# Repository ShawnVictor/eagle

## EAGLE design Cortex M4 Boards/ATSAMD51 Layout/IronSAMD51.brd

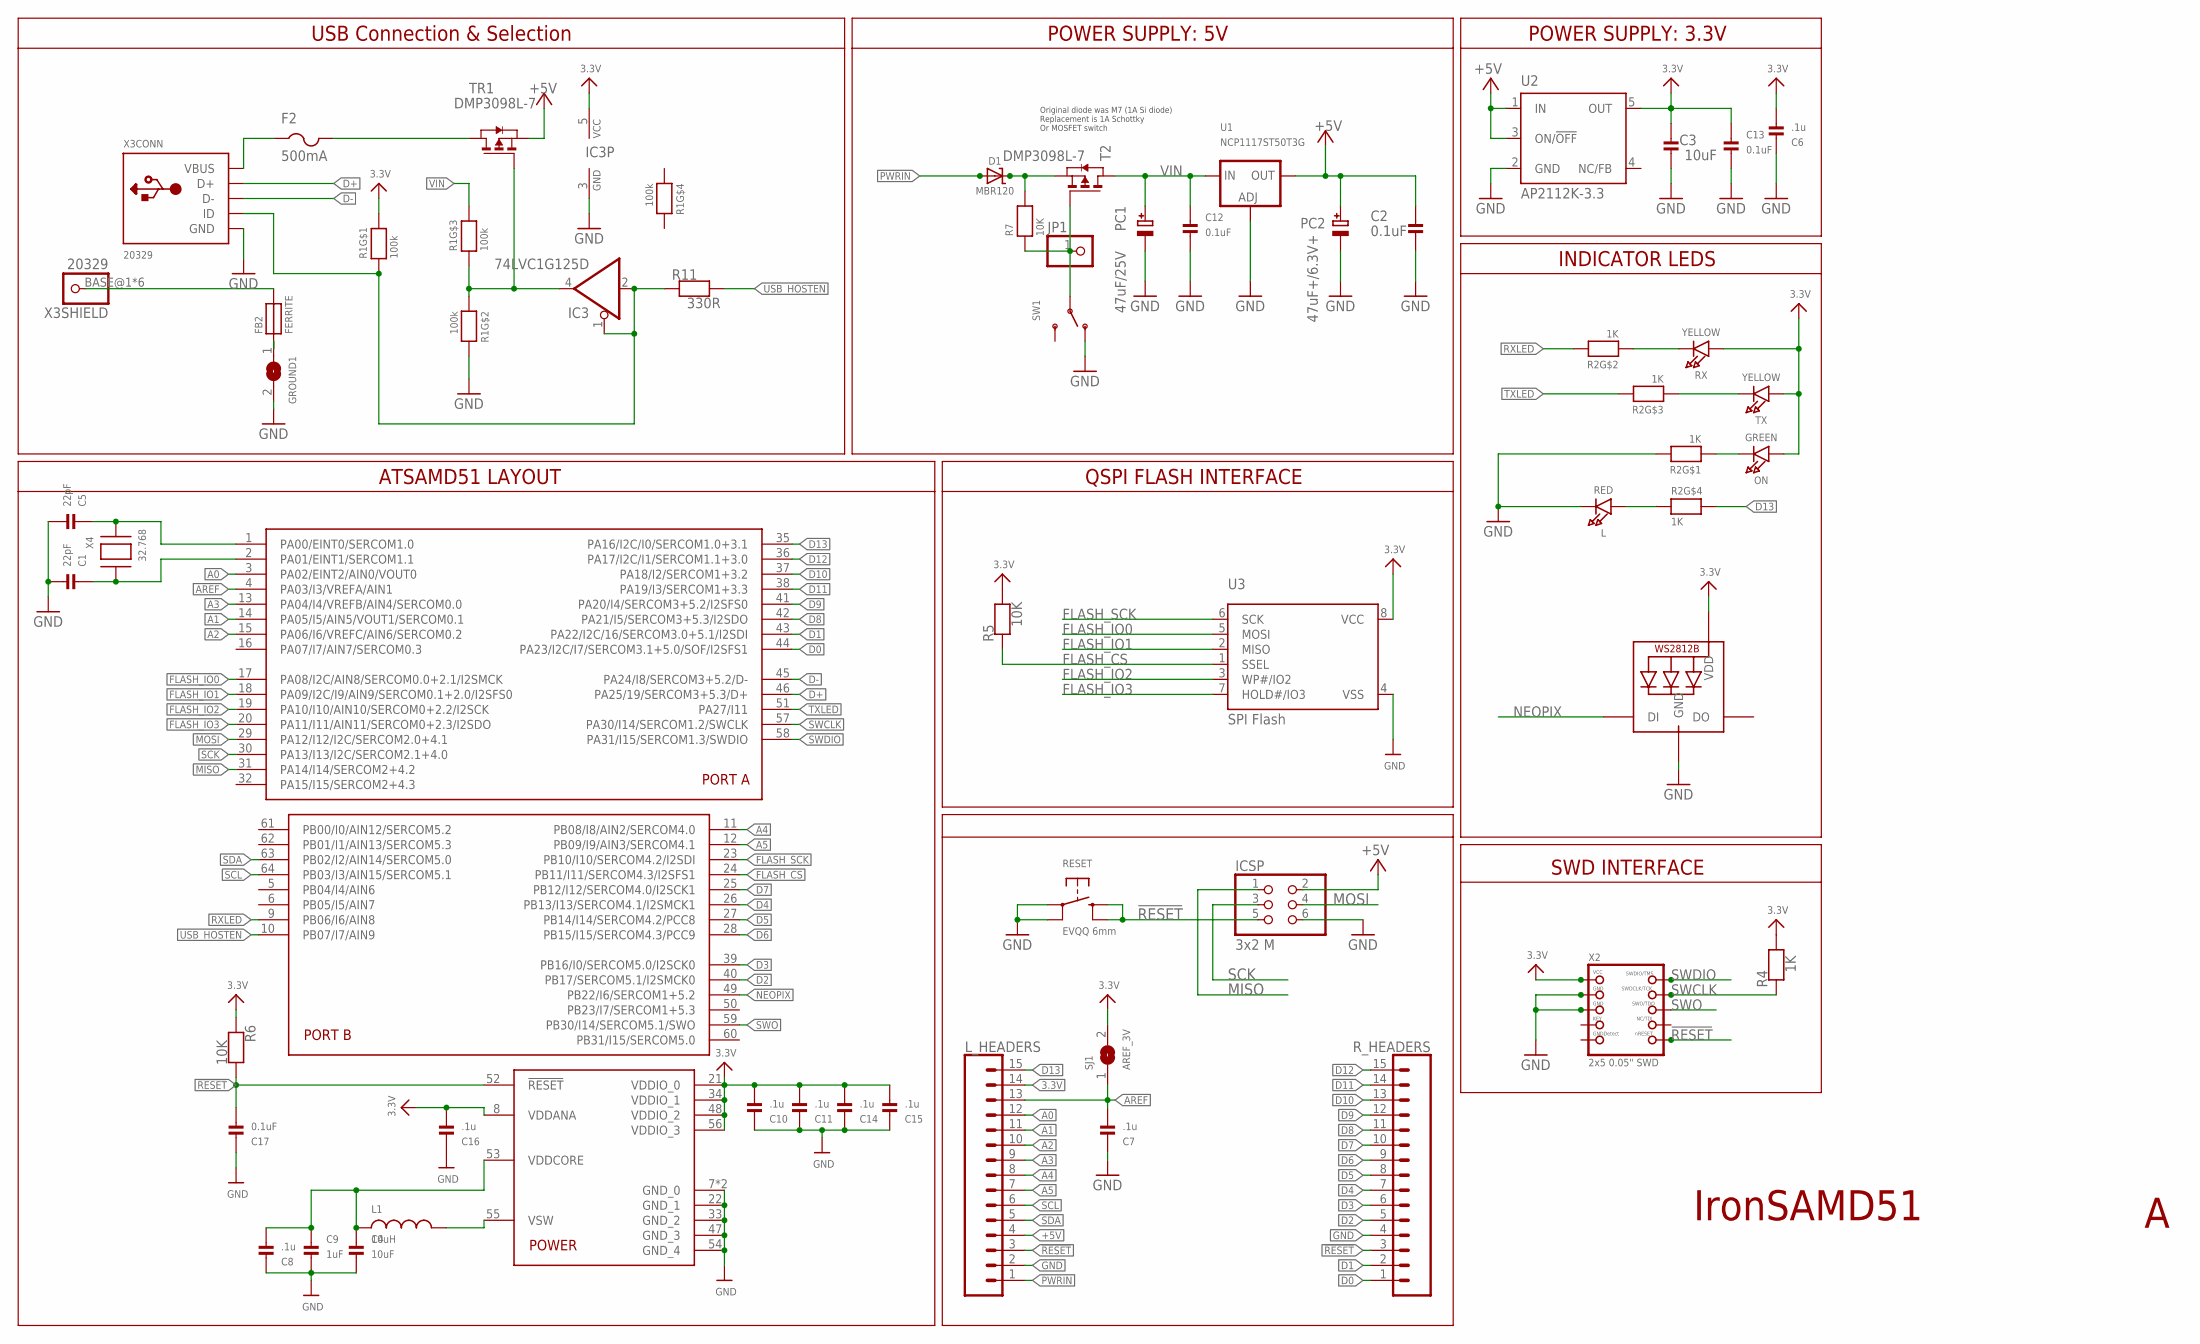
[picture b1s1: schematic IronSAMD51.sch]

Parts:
C1, C5: 22pF; 0603
C2: 0.1uF; 0805
C3, C4: 10uF; 0805
C6, C7, C8, C10, C11, C14, C15, C16: .1u; 0603
C9: 1uF; 0603
C12, C13, C17: 0.1uF; 0603
D1: MBR120; SOD-123
F2: 500mA; R1206
FB2: FERRITE; 0603
GROUND1: SOLDERJUMPERCLOSED; SOLDERJUMPER_CLOSEDWIRE
IC3: 74LVC1G125D; SOT23-5
ICSP: 3x2 M; 2X03_ROUND_70MIL
JP1: HEADER-1X1ROUND; 1X01_ROUND
L: RED; CHIPLED_0805_NOOUTLINE
L1: 10uH; INDUCTOR_1007
LED1: WS2812B3535; LED3535
L_HEADERS: CONN_15; 1X15
ON: GREEN; CHIPLED_0805_NOOUTLINE
PC1: 47uF/25V; PANASONIC_D
PC2: 47uF+/6.3V+; PANASONIC_D
R1: 100k; RESPACK_4X0603
R2: 1K; RESPACK_4X0603
R4: 1K; 0603
R5, R6, R7: 10K; 0603
R11: 330R; 0603
RESET: EVQQ 6mm; EVQ-Q2
RX: YELLOW; CHIPLED_0805_NOOUTLINE
R_HEADERS: CONN_15; 1X15
SJ1: AREF_3V; SOLDERJUMPER_CLOSEDWIRE
SW1: SWITCH_SPDT; SPDT_SMT_SSSS811101
T2: DMP3098L-7; SOT-23
TR1: DMP3098L-7; SOT-23
TX: YELLOW; CHIPLED_0805_NOOUTLINE
U1: NCP1117ST50T3G; SOT223-R
U2: AP2112K-3.3; SOT23-DBV
U3: SPI Flash; SOIC8_208MIL
U$3: ATSAMD51J; PQFN64-1
X2: 2x5 0.05" SWD; 2X05_1.27MM_BOX_POSTS
X3: 20329; 4UCONN_20329_V2
X4: 32.768; XTAL3215

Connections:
3.3V: C3.2, C6.2, C10.2, C11.2, C13.1, C14.2, C15.2, C16.2, IC3.5 (VCC), LED1.2 (VDD), L_HEADERS.14, ON.A, R1.8 (2), R4.2, R5.2, R6.1, RX.A, SJ1.2, TX.A, U2.5 (OUT), U3.8 (VCC), U$3.8 (VDDANA), U$3.21 (VDDIO_0), U$3.34 (VDDIO_1), U$3.48 (VDDIO_2), U$3.56 (VDDIO_3), X2.1 (VCC)
!RESET: C17.2, ICSP.5, L_HEADERS.3, R6.2, RESET.B (S), RESET.B' (S1), R_HEADERS.3, U$3.52 (!RESET), X2.10 (NRESET)
+5V: C2.2, ICSP.2, L_HEADERS.4, PC2.+, TR1.2 (S), U1.2 (OUT), U1.4 (OUT), U2.1 (IN), U2.3 (ON/!OFF)
A0: L_HEADERS.12, U$3.3 (PA02/EINT2/AIN0/VOUT0)
A1: L_HEADERS.11, U$3.14 (PA05/I5/AIN5/VOUT1/SERCOM0.1)
A2: L_HEADERS.10, U$3.15 (PA06/I6/VREFC/AIN6/SERCOM0.2)
A3: L_HEADERS.9, U$3.13 (PA04/I4/VREFB/AIN4/SERCOM0.0)
A4: L_HEADERS.8, U$3.11 (PB08/I8/AIN2/SERCOM4.0)
A5: L_HEADERS.7, U$3.12 (PB09/I9/AIN3/SERCOM4.1)
AREF: C7.2, L_HEADERS.13, SJ1.1, U$3.4 (PA03/I3/VREFA/AIN1)
D0: R_HEADERS.1, U$3.44 (PA23/I2C/I7/SERCOM3.1+5.0/SOF/I2SFS1)
D1: R_HEADERS.2, U$3.43 (PA22/I2C/16/SERCOM3.0+5.1/I2SDI)
D2: R_HEADERS.5, U$3.40 (PB17/SERCOM5.1/I2SMCK0)
D3: R_HEADERS.6, U$3.39 (PB16/I0/SERCOM5.0/I2SCK0)
D4: R_HEADERS.7, U$3.26 (PB13/I13/SERCOM4.1/I2SMCK1)
D5: R_HEADERS.8, U$3.27 (PB14/I14/SERCOM4.2/PCC8)
D6: R_HEADERS.9, U$3.28 (PB15/I15/SERCOM4.3/PCC9)
D7: R_HEADERS.10, U$3.25 (PB12/I12/SERCOM4.0/I2SCK1)
D8: R_HEADERS.11, U$3.42 (PA21/I5/SERCOM3+5.3/I2SDO)
D9: R_HEADERS.12, U$3.41 (PA20/I4/SERCOM3+5.2/I2SFS0)
D10: R_HEADERS.13, U$3.37 (PA18/I2/SERCOM1+3.2)
D11: R_HEADERS.14, U$3.38 (PA19/I3/SERCOM1+3.3)
D12: R_HEADERS.15, U$3.36 (PA17/I2C/I1/SERCOM1.1+3.0)
D13: L_HEADERS.15, R2.5 (2), U$3.35 (PA16/I2C/I0/SERCOM1.0+3.1)
D+: U$3.46 (PA25/19/SERCOM3+5.3/D+), X3.D+
D-: U$3.45 (PA24/I8/SERCOM3+5.2/D-), X3.D-
FLASH_CS: R5.1, U3.1 (SSEL), U$3.24 (PB11/I11/SERCOM4.3/I2SFS1)
FLASH_IO0: U3.5 (MOSI), U$3.17 (PA08/I2C/AIN8/SERCOM0.0+2.1/I2SMCK)
FLASH_IO1: U3.2 (MISO), U$3.18 (PA09/I2C/I9/AIN9/SERCOM0.1+2.0/I2SFS0)
FLASH_IO2: U3.3 (WP#/IO2), U$3.19 (PA10/I10/AIN10/SERCOM0+2.2/I2SCK)
FLASH_IO3: U3.7 (HOLD#/IO3), U$3.20 (PA11/I11/AIN11/SERCOM0+2.3/I2SDO)
FLASH_SCK: U3.6 (SCK), U$3.23 (PB10/I10/SERCOM4.2/I2SDI)
GND: C1.2, C2.1, C3.1, C4.2, C5.2, C6.1, C7.1, C8.1, C9.2, C10.1, C11.1, C12.2, C13.2, C14.1, C15.1, C16.1, C17.1, GROUND1.2, IC3.3 (GND), ICSP.6, L.C, LED1.4 (GND), L_HEADERS.2, PC1.-, PC2.-, R1.7 (2), R2.8 (2), RESET.A, RESET.A' (P1), R_HEADERS.4, SW1.A (O), U1.1 (ADJ), U2.2 (GND), U3.4 (VSS), U$3.7 (GND_0), U$3.22 (GND_1), U$3.33 (GND_2), U$3.47 (GND_3), U$3.54 (GND_4), U$3.EXP (GND_0), X2.3 (GND), X2.5 (GND), X3.GND
MISO: ICSP.1, U$3.31 (PA14/I14/SERCOM2+4.2)
MOSI: ICSP.4, U$3.29 (PA12/I12/I2C/SERCOM2.0+4.1)
unnamed: F2.1, X3.VBUS
unnamed: F2.2, TR1.1 (D)
unnamed: IC3.4 (O), R1.2 (1), R1.3 (1), TR1.3 (G)
unnamed: ON.C, R2.1
unnamed: FB2.1, GROUND1.1
unnamed: R2.2 (1), RX.C
unnamed: R2.3 (1), TX.C
unnamed: L.A, R2.4 (1)
unnamed: IC3.1 (OE), IC3.2 (I), R1.1, R11.1, X3.ID
unnamed: C5.1, U$3.1 (PA00/EINT0/SERCOM1.0), X4.P$1
unnamed: C1.1, U$3.2 (PA01/EINT1/SERCOM1.1), X4.P$2
unnamed: L1.P$2 (2), U$3.55 (VSW)
unnamed: C4.1, C8.2, C9.1, L1.P$1 (1), U$3.53 (VDDCORE)
unnamed: D1.C, R7.2, T2.2 (S)
NEOPIX: LED1.1 (DI), U$3.49 (PB22/I6/SERCOM1+5.2)
PWRIN: D1.A, L_HEADERS.1
PWR_SWITCH: JP1.1, R7.1, SW1.B, T2.3 (G)
RXLED: R2.7 (2), U$3.9 (PB06/I6/AIN8)
SCK: ICSP.3, U$3.30 (PA13/I13/I2C/SERCOM2.1+4.0)
SCL: L_HEADERS.6, U$3.64 (PB03/I3/AIN15/SERCOM5.1)
SDA: L_HEADERS.5, U$3.63 (PB02/I2/AIN14/SERCOM5.0)
SWCLK: R4.1, U$3.57 (PA30/I14/SERCOM1.2/SWCLK), X2.4 (SWDCLK)
SWDIO: U$3.58 (PA31/I15/SERCOM1.3/SWDIO), X2.2 (SWDIO)
SWO: U$3.59 (PB30/I14/SERCOM5.1/SWO), X2.6 (SWO)
TXLED: R2.6 (2), U$3.51 (PA27/I11)
USB_HOSTEN: R11.2, U$3.10 (PB07/I7/AIN9)
USHIELD: FB2.2, X3.BASE@1 (1), X3.BASE@2 (1), X3.SPRT@1 (1), X3.SPRT@2 (1), X3.SPRT@3 (1), X3.SPRT@4 (1)
VIN: C12.1, PC1.+, R1.6 (2), T2.1 (D), U1.3 (IN)

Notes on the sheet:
USB Connection & Selection
Original diode was M7 (1A Si diode) Replacement is 1A Schottky Or MOSFET switch
POWER SUPPLY: 5V
INDICATOR LEDS
POWER SUPPLY: 3.3V
SWD INTERFACE
QSPI FLASH INTERFACE
ATSAMD51 LAYOUT
IronSAMD51

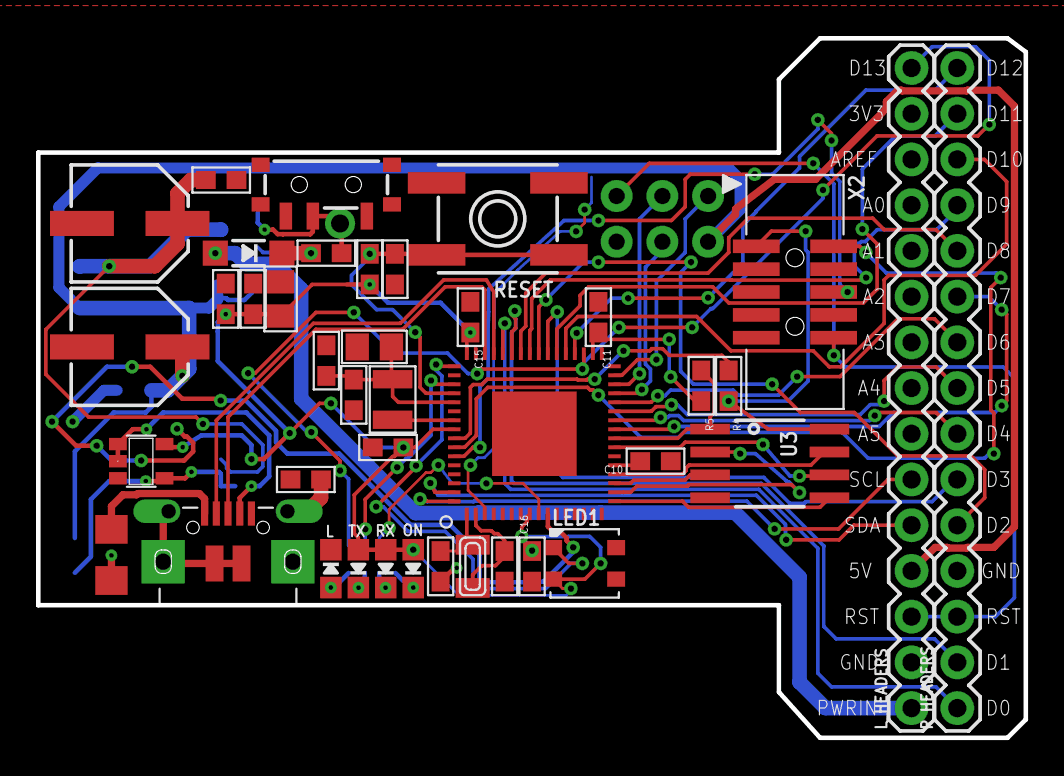
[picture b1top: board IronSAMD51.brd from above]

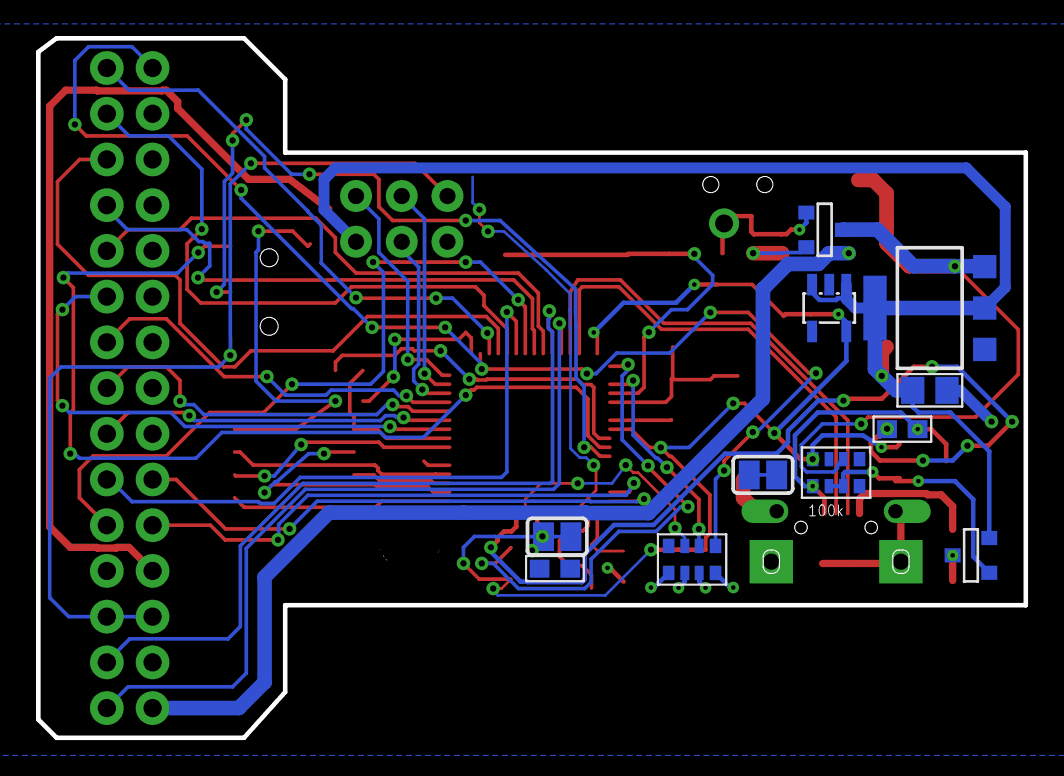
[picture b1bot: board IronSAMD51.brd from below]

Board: 2 copper layers, 54.9 x 38.9 mm, 53 parts (11 on the bottom side), 63 nets.

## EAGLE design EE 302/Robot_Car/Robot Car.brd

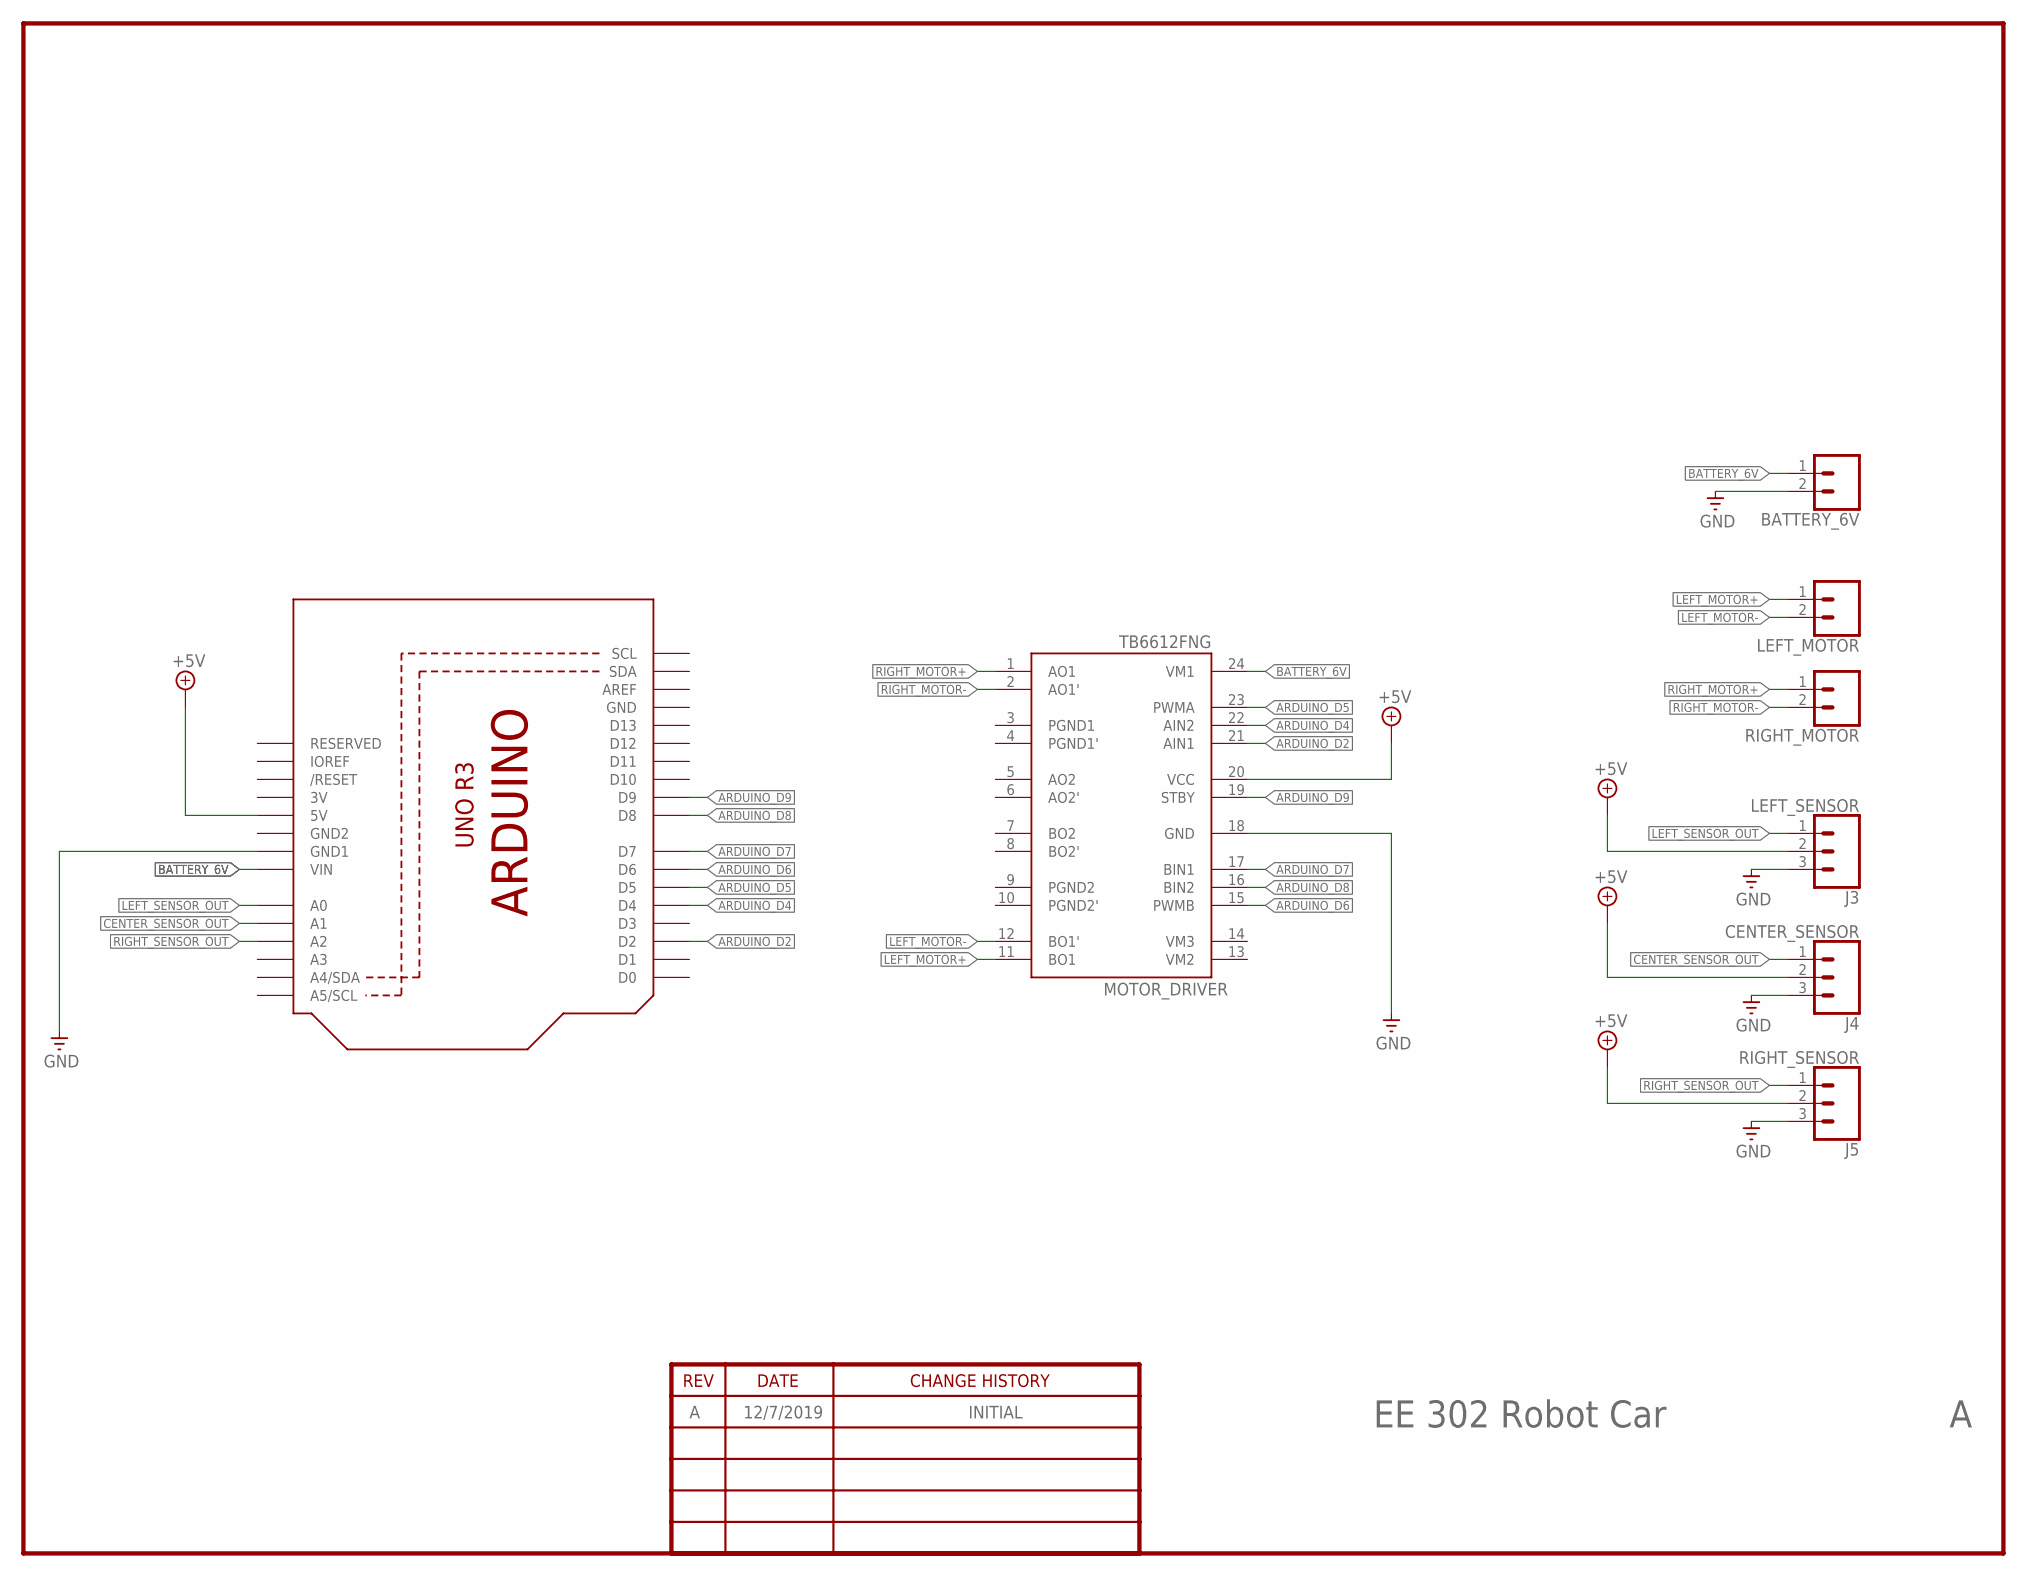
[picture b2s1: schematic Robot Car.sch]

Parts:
BATTERY_6V: CONN_02; 1X02
J3: LEFT_SENSOR; 1X03
J4: CENTER_SENSOR; 1X03
J5: RIGHT_SENSOR; 1X03
LEFT_MOTOR: CONN_02; 1X02
MOTOR_DRIVER: TB6612FNG; SSOP24
RIGHT_MOTOR: CONN_02; 1X02
U1: ARDUINOR3-DIMENSION; ARDUINOR3

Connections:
3V: U1.3V
+5V: J3.2, J4.2, J5.2, MOTOR_DRIVER.20 (VCC), U1.5V
ARDUINO_D2: MOTOR_DRIVER.21 (AIN1), U1.D2
ARDUINO_D4: MOTOR_DRIVER.22 (AIN2), U1.D4
ARDUINO_D5: MOTOR_DRIVER.23 (PWMA), U1.D5
ARDUINO_D6: MOTOR_DRIVER.15 (PWMB), U1.D6
ARDUINO_D7: MOTOR_DRIVER.17 (BIN1), U1.D7
ARDUINO_D8: MOTOR_DRIVER.16 (BIN2), U1.D8
ARDUINO_D9: MOTOR_DRIVER.19 (STBY), U1.D9
BATTERY_6V: BATTERY_6V.1, MOTOR_DRIVER.24 (VM1), U1.VIN
CENTER_SENSOR_OUT: J4.1, U1.A1
GND: BATTERY_6V.2, J3.3, J4.3, J5.3, MOTOR_DRIVER.18 (GND), U1.GND, U1.GND1
GND2: U1.GND2
LEFT_MOTOR+: LEFT_MOTOR.1, MOTOR_DRIVER.11 (BO1)
LEFT_MOTOR-: LEFT_MOTOR.2, MOTOR_DRIVER.12 (BO1')
LEFT_SENSOR_OUT: J3.1, U1.A0
PGND1: MOTOR_DRIVER.3 (PGND1)
PGND1': MOTOR_DRIVER.4 (PGND1')
PGND2: MOTOR_DRIVER.9 (PGND2)
PGND2': MOTOR_DRIVER.10 (PGND2')
RIGHT_MOTOR+: MOTOR_DRIVER.1 (AO1), RIGHT_MOTOR.1
RIGHT_MOTOR-: MOTOR_DRIVER.2 (AO1'), RIGHT_MOTOR.2
RIGHT_SENSOR_OUT: J5.1, U1.A2
VM2: MOTOR_DRIVER.13 (VM2)
VM3: MOTOR_DRIVER.14 (VM3)

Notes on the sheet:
EE 302 Robot Car
12/7/2019
INITIAL

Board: 2 copper layers, 8 parts (0 on the bottom side), 17 nets, no tracks yet.

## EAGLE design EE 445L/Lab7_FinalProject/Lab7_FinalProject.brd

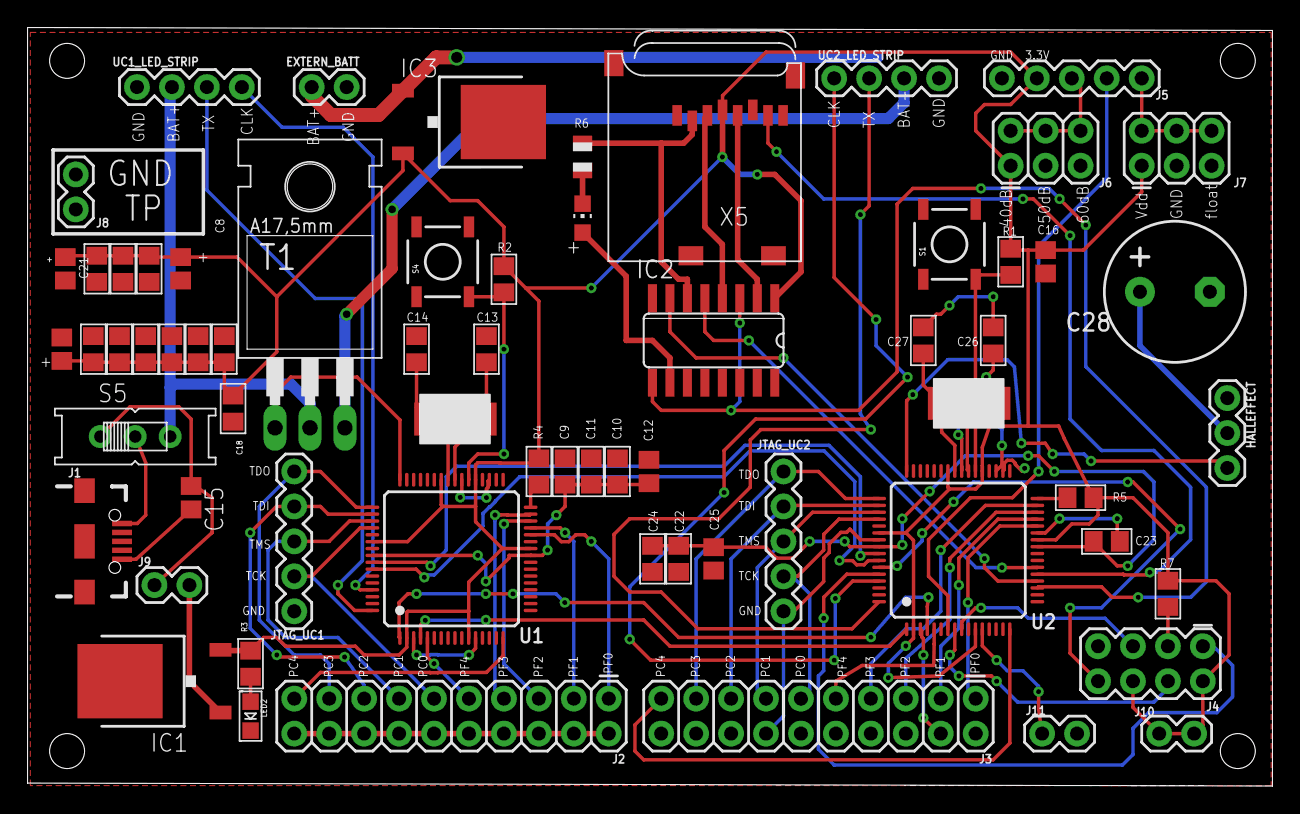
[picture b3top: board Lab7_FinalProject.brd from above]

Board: 2 copper layers, 90.5 x 55.1 mm, 66 parts (0 on the bottom side), 65 nets.

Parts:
ACT: RED; CHIP-LED0805
C1, C3, C5, C18: 0.01uF; 0805
C2: 10uF/10V; C0805
C4, C6, C9, C10, C17, C19, C22, C23: 0.1uF; 0805
C7, C11, C20, C24: 1uF; 0805
C8, C21: 0.01uF; C0805
C12, C25: 2.2uF; C0805
C13, C14, C26, C27: 10pF; 0805
C15: 4.7uF; C0805
C16: 4,7uF; C0805
C28: 1000uF; E-050X100
EXTERN_BATT: 1X02
HALLEFFECT: 1X03
IC1: 7812DT; TO252
IC2: 4050D; SO16
IC3: 3.3VReg1; TO252
J1: USB-B-MICRO-SMD
J2: LA1; 2X10
J3: LA2; 2X10
J4: ESP8266; 2X4
J5: MICROPHONE; 1X05
J6: GAIN SELECT; 2X3
J7: A/R SELECT; 2X3
J8, J9: 1X02
J10: 3.3V TESTPOINT; 1X02
J11: GND TESTPOINT; 1X02
JTAG_UC1, JTAG_UC2: 1X05
LED2: CHIPLED_0805
R1, R2, R7: 10k; 0805
R3: 1k; 0805
R4, R5: 1M; 0805
R6: 1K; R0805
S1, S4: MOMENTARY_SW; TACTILE_SWITCH_SMD
S5: EG1218
T1: TIP31; TO220
U1, U2: TM4C123GH6PM; LQFP64
U$45, U$48: NX5032GA-16MHZCRYSTAL
UC1_LED_STRIP, UC2_LED_STRIP: 1X04
X5: MICROSD

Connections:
3.3V: C1.1, C2.1, C3.1, C4.1, C5.1, C6.1, C7.1, C8.1, C16.1, C17.1, C18.1, C19.1, C20.1, C21.1, IC1.2, IC2.1, IC3.2, J4.2, J4.6, J5.4, J6.1, J7.1, J10.1, J10.2, R1.2, R2.2, R3.2, R4.2, R5.2, R7.2, U1.2, U1.11, U1.26, U1.37, U1.42, U1.54, U2.2, U2.11, U2.26, U2.37, U2.42, U2.54, X5.4
BATT_IN: C28.+, EXTERN_BATT.2, HALLEFFECT.2, IC3.1, S5.S, T1.2, UC1_LED_STRIP.3
ESP_GPIO0: J4.3, R7.1
GND: C1.2, C2.2, C3.2, C4.2, C5.2, C6.2, C7.2, C8.2, C9.2, C10.2, C11.2, C12.2, C13.1, C14.1, C15.2, C16.2, C17.2, C18.2, C19.2, C20.2, C21.2, C22.2, C23.2, C24.2, C25.2, C26.1, C27.1, C28.-, EXTERN_BATT.1, HALLEFFECT.1, IC1.3, IC2.8, IC2.11, IC2.14, IC3.3, J1.GND, J2.2, J2.4, J2.6, J2.8, J2.10, J2.12, J2.14, J2.16, J2.18, J2.20, J3.2, J3.4, J3.6, J3.8, J3.10, J3.12, J3.14, J3.16, J3.18, J3.20, J4.7, J5.5, J6.3, J7.3, J8.1, J8.2, J11.1, J11.2, JTAG_UC1.1, JTAG_UC2.1, LED2.C, S1.1, S4.1, U1.3, U1.12, U1.27, U1.34, U1.35, U1.39, U1.55, U2.3, U2.12, U2.27, U2.34, U2.35, U2.39, U2.55, UC1_LED_STRIP.4, UC2_LED_STRIP.4, X5.6, X5.MT1, X5.MT2
LED_PW_IN: T1.3, UC2_LED_STRIP.3
MIC_AR: J5.1, J7.2, J7.4, J7.6
MIC_GAIN: J5.3, J6.2, J6.4, J6.6
unnamed: C13.2, U1.40, U$45.P$1
unnamed: C9.1, C10.1, C11.1, C12.1, U1.25, U1.56
unnamed: C26.2, U2.40, U$48.P$1
unnamed: ACT.A, IC2.10
unnamed: IC2.2, X5.5
unnamed: C22.1, C23.1, C24.1, C25.1, U2.25, U2.56
unnamed: C27.2, U2.41, U$48.P$2
unnamed: R1.1, S1.3, U2.38
unnamed: R5.1, U2.32
unnamed: IC2.6, R6.1, X5.2
unnamed: ACT.C, R6.2
unnamed: IC2.4, X5.3
unnamed: IC1.1, J9.2
OSC1: C14.2, U1.41, U$45.P$2
POWER_IN: C15.1, J9.1, S5.O
POWER_LED: LED2.A, R3.1
RESET: R2.1, S4.3, U1.38
UC1_PB3/LED_SW: T1.1, U1.48
UC1_PC0/TCK: J2.11, JTAG_UC1.2, U1.52
UC1_PC1/TMS: J2.13, JTAG_UC1.3, U1.51
UC1_PC2/TDI: J2.15, JTAG_UC1.4, U1.50
UC1_PC3/TDO: J2.17, JTAG_UC1.5, U1.49
UC1_PC4: J2.19, U1.16
UC1_PD0/SSI3_CLK: U1.61, UC1_LED_STRIP.1
UC1_PD3/SSI3_TX: U1.64, UC1_LED_STRIP.2
UC1_PF0: J2.1, U1.28
UC1_PF1: J2.3, U1.29
UC1_PF2: J2.5, U1.30
UC1_PF3: J2.7, U1.31
UC1_PF4: J2.9, U1.5
UC2_PA2/SDCARD_CLK: IC2.3, IC2.9, U2.19
UC2_PA3/SDCARD_CS: IC2.7, U2.20
UC2_PA4/SDCARD_DO: U2.21, X5.7
UC2_PA5/SDCARD_DI: IC2.5, U2.22
UC2_PB3/HALLEFFECT: HALLEFFECT.3, U2.48
UC2_PC0/TCK: J3.11, JTAG_UC2.2, U2.52
UC2_PC1/TMS: J3.13, JTAG_UC2.3, U2.51
UC2_PC2/TDI: J3.15, JTAG_UC2.4, U2.50
UC2_PC3/TDO: J3.17, JTAG_UC2.5, U2.49
UC2_PC4: J3.19, U2.16
UC2_PD0/SSI3_CLK: U2.61, UC2_LED_STRIP.1
UC2_PD3/SSI3_TX: U2.64, UC2_LED_STRIP.2
UC2_PE0/ESP_GPIO2: J4.5, U2.9
UC2_PE1/ESP_RESET: J4.4, U2.8
UC2_PE2/MIC_OUT: J5.2, U2.7
UC2_PE4/ESP_TX: J4.8, U2.59
UC2_PE5/ESP_RX: J4.1, U2.60
UC2_PF0: J3.1, U2.28
UC2_PF1: J3.3, U2.29
UC2_PF2: J3.5, U2.30
UC2_PF3: J3.7, U2.31
UC2_PF4: J3.9, U2.5
UC12_PB4/CLK: U1.58, U2.58
UC12_PB5/FSS: U1.57, U2.57
UC12_PB6/7/RX2TX: U1.1, U2.4
UC12_PB6/7/TX2RX: U1.4, U2.1
VBUS: J1.VBUS, S5.P
WAKE: R4.1, U1.32

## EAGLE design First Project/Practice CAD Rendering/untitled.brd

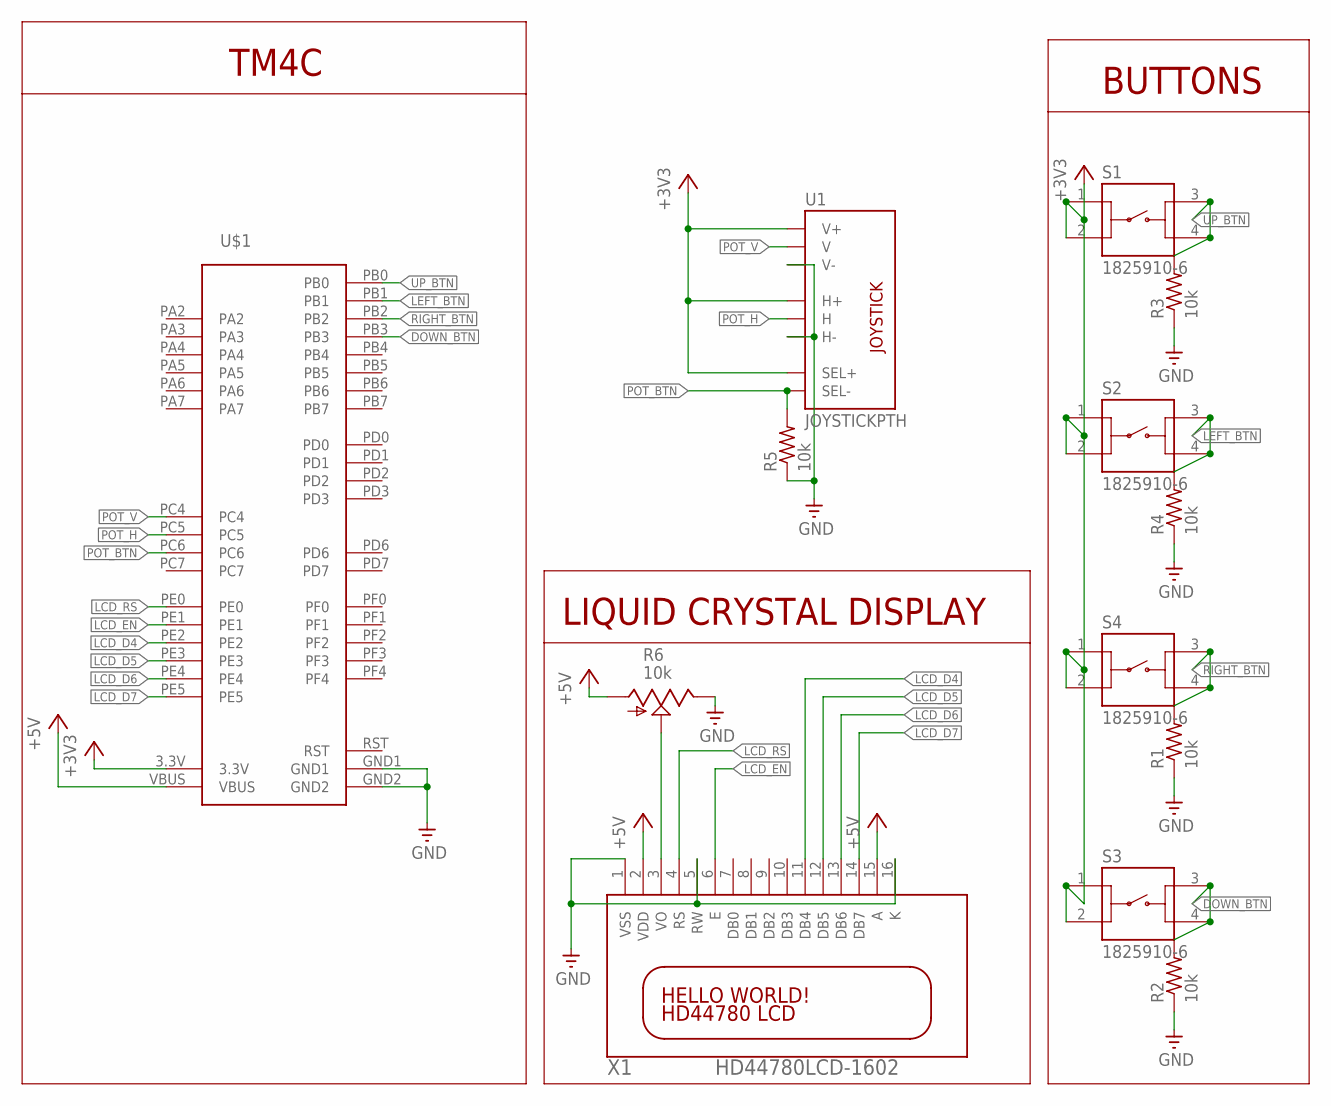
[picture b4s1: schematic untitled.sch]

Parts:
R1, R2, R3, R4, R5: 10k; R0805
R6: 10k; S64W
S1, S2, S3, S4: 1825910-6
U1: JOYSTICKPTH; JOYSTICK
U$1: STELLARIS-LAUNCHPADSTELLARIS-LAUNCHPAD; LAUNCHPAD-XL
X1: HD44780LCD-1602; LCD1602

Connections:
+3V3: S1.1, S1.2, S2.1, S2.2, S3.1, S3.2, S4.1, S4.2, U1.B1A (SEL+), U1.H1 (H+), U1.V1 (V+), U$1.3.3V
+5V: R6.A, U$1.VBUS, X1.2 (VDD), X1.15 (A)
DOWN_BTN: R2.2, S3.3, S3.4, U$1.PB3
GND: R1.1, R2.1, R3.1, R4.1, R5.1, R6.E, U1.H3 (H-), U1.V3 (V-), U$1.GND1, U$1.GND2, X1.1 (VSS), X1.5 (RW), X1.16 (K)
LCD_D4: U$1.PE2, X1.11 (DB4)
LCD_D5: U$1.PE3, X1.12 (DB5)
LCD_D6: U$1.PE4, X1.13 (DB6)
LCD_D7: U$1.PE5, X1.14 (DB7)
LCD_EN: U$1.PE1, X1.6 (E)
LCD_RS: U$1.PE0, X1.4 (RS)
LEFT_BTN: R4.2, S2.3, S2.4, U$1.PB1
unnamed: R6.S, X1.3 (VO)
POT_BTN: R5.2, U1.B2A (SEL-), U$1.PC6
POT_H: U1.H2 (H), U$1.PC5
POT_V: U1.V2 (V), U$1.PC4
RIGHT_BTN: R1.2, S4.3, S4.4, U$1.PB2
RST: U$1.RST
UP_BTN: R3.2, S1.3, S1.4, U$1.PB0

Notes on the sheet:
TM4C
LIQUID CRYSTAL DISPLAY
BUTTONS

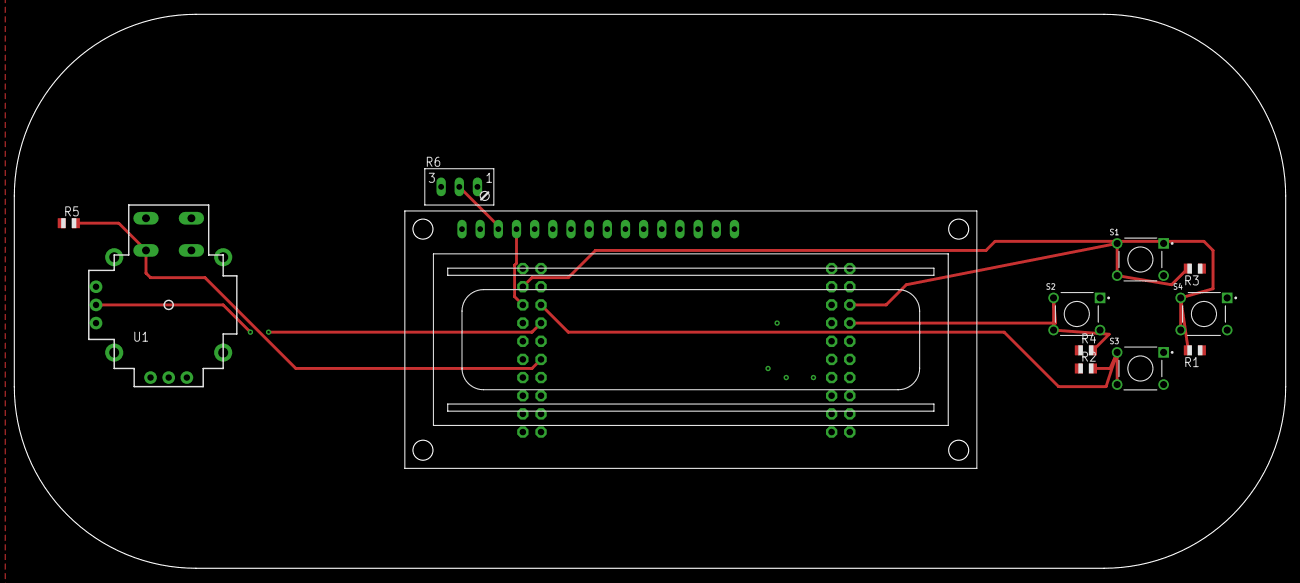
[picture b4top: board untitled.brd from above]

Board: 2 copper layers, 177.8 x 77.5 mm, 13 parts (1 on the bottom side), 17 nets.

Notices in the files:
parts and their libraries:
microbuilder: This work is placed in the public domain, and may be freely used for commercial and non-commercial work with the following conditions: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
SparkFun-Connectors: Licensing: Creative Commons ShareAlike 4.0 International - https://creativecommons.org/licenses/by-sa/4.0
